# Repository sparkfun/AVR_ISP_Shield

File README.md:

SparkFun AVR ISP Shield
========================

[*SparkFun AVR ISP Shield (DEV-11168)*](https://www.sparkfun.com/products/11168)

This shield, once assembled, gives your Arduino a 28-pin ZIF (Zero Insertion Force) socket so it can grab onto unsuspecting ICs. 
The socket is wired to work directly with the ArduinoISP code, but burning bootloaders isn’t the only thing you can do with it. 
We’ve also connected the serial I/Os so that if you’re a programming ninja you can do cool tricks like programming ICs using the bootloader on-the-go.

Repository Contents
-------------------
* **/Hardware** - All Eagle design files (.brd, .sch)

License Information
-------------------
The hardware is released under [Creative Commons ShareAlike 4.0 International](https://creativecommons.org/licenses/by-sa/4.0/).

Distributed as-is; no warranty is given.

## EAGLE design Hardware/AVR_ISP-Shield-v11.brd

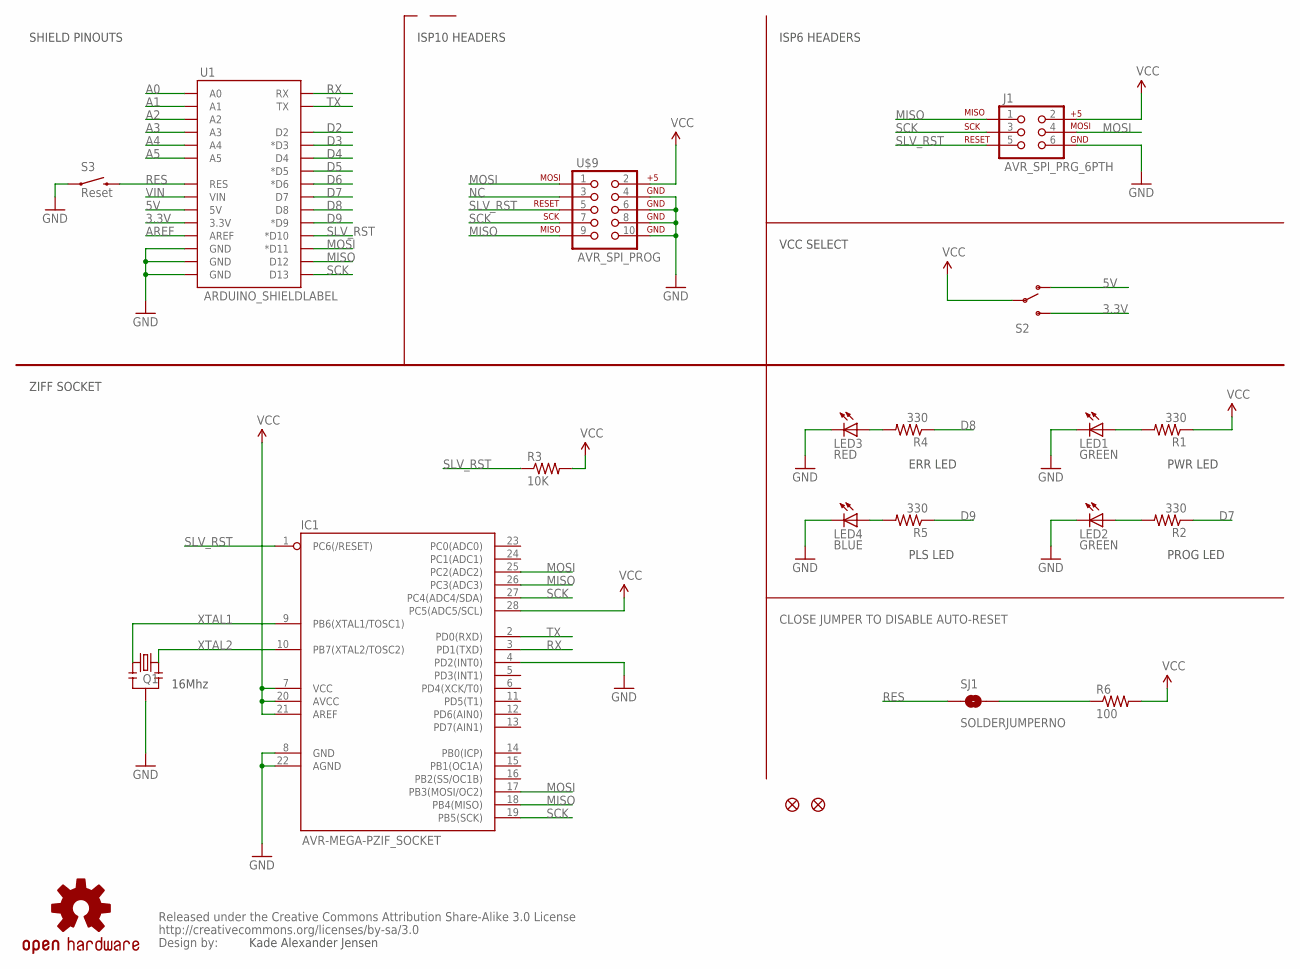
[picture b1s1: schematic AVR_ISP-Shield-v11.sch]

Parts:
$$U$1: CREATIVE_COMMONS
IC1: AVR-MEGA-PZIF_SOCKET; DIL28-3-ZIF_SOCKET
J1: AVR_SPI_PRG_6PTH; 2X3
JP5, JP6: FIDUCIAL1X2.5; FIDUCIAL-1X2.5
LED1, LED2: GREEN; LED-0603
LED3: RED; LED-0603
LED4: BLUE; LED-0603
Q1: 8/16/20MHz; RESONATOR-SMD
R1, R2, R4, R5: 330; 0402-RES
R3: 10K; 0402-RES
R6: 100; 0402-RES
S2: SWITCH-SPSTSMD; AYZ0202
S3: Reset; TACTILE_SWITCH_SMD
SJ1: SOLDERJUMPERNO; SJ_2S-NO
U1: ARDUINO_SHIELDLABEL; DUEMILANOVE_SHIELD
U$4: OSHW-LOGOS; OSHW-LOGO-S
U$9: AVR_SPI_PROG; AVR_ICSP

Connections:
3.3V: S2.3 (S), U1.3.3V
5V: S2.1 (O), U1.5V
A0: U1.A0
A1: U1.A1
A2: U1.A2
A3: U1.A3
A4: U1.A4
A5: U1.A5
AREF: U1.AREF
D2: U1.D2
D3: U1.D3 (*D3)
D4: U1.D4
D5: U1.D5 (*D5)
D6: U1.D6 (*D6)
D7: R2.1, U1.D7
D8: R4.1, U1.D8
D9: R5.1, U1.D9 (*D9)
GND: IC1.4 (PD2(INT0)), IC1.8 (GND), IC1.22 (AGND), J1.6, LED1.C, LED2.C, LED3.C, LED4.C, Q1.2, S3.1, U1.GND@0 (GND), U1.GND@1 (GND), U1.GND@2 (GND), U$9.4, U$9.6, U$9.8, U$9.10
MISO: IC1.18 (PB4(MISO)), IC1.26 (PC3(ADC3)), J1.1, U1.D12, U$9.9
MOSI: IC1.17 (PB3(MOSI/OC2)), IC1.25 (PC2(ADC2)), J1.4, U1.D11 (*D11), U$9.1
unnamed: LED1.A, R1.2
unnamed: LED2.A, R2.2
unnamed: LED3.A, R4.2
unnamed: LED4.A, R5.2
unnamed: R6.1, SJ1.2
NC: U$9.3
RES: S3.3 (2), SJ1.1, U1.RES
RX: IC1.3 (PD1(TXD)), U1.RX
SCK: IC1.19 (PB5(SCK)), IC1.27 (PC4(ADC4/SDA)), J1.3, U1.D13, U$9.7
SLV_RST: IC1.1 (PC6(/RESET)), J1.5, R3.1, U1.D10 (*D10), U$9.5
TX: IC1.2 (PD0(RXD)), U1.TX
VCC: IC1.7 (VCC), IC1.20 (AVCC), IC1.21 (AREF), IC1.28 (PC5(ADC5/SCL)), J1.2, R1.1, R3.2, R6.2, S2.2, U$9.2
VIN: U1.VIN
XTAL1: IC1.9 (PB6(XTAL1/TOSC1)), Q1.3
XTAL2: IC1.10 (PB7(XTAL2/TOSC2)), Q1.1

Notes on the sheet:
PWR LED
PROG LED
VCC SELECT
ISP6 HEADERS
ERR LED
PLS LED
16Mhz
Kade Alexander Jensen
ZIFF SOCKET
SHIELD PINOUTS
ISP10 HEADERS
CLOSE JUMPER TO DISABLE AUTO-RESET

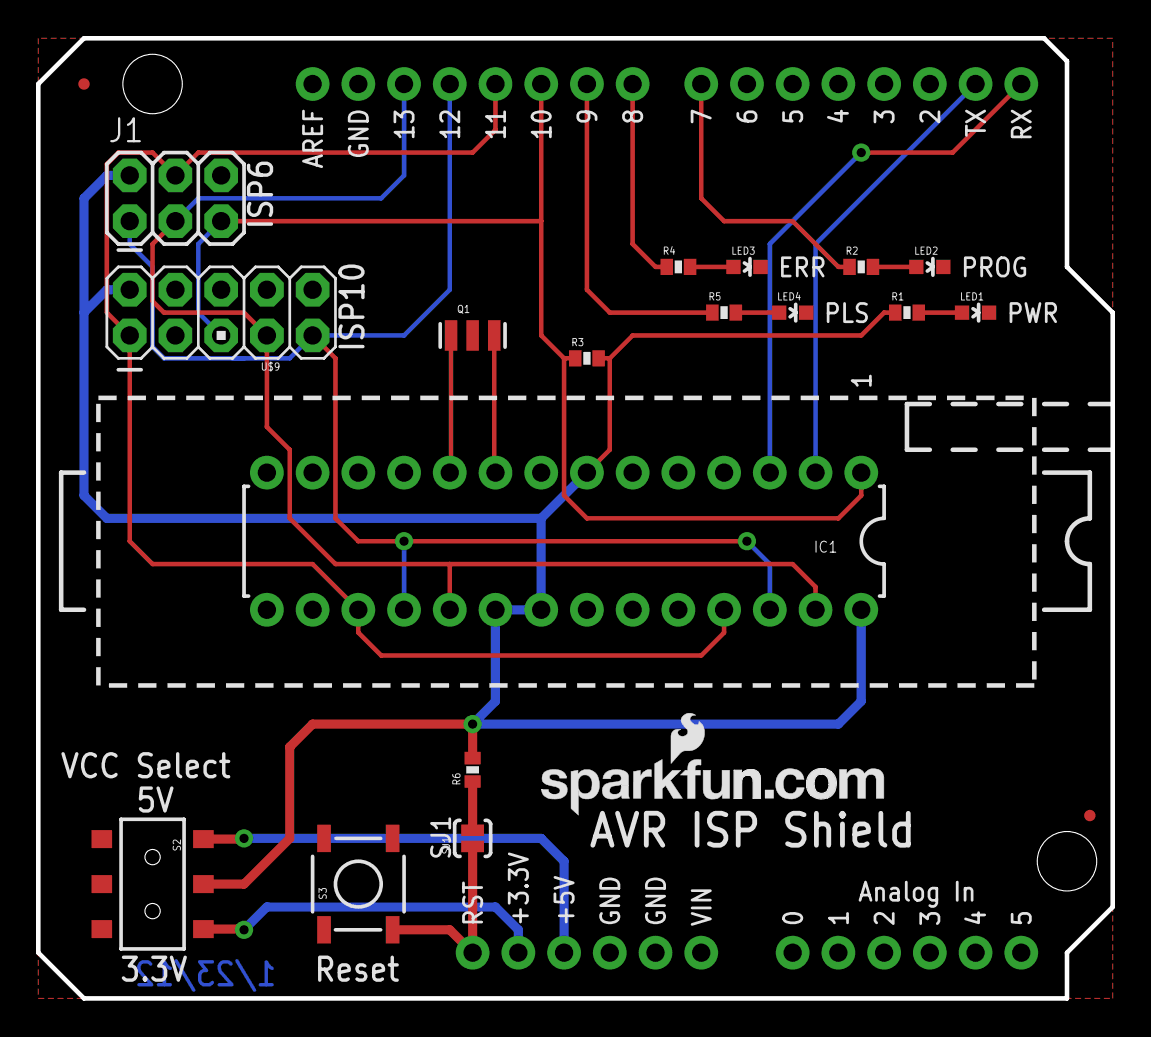
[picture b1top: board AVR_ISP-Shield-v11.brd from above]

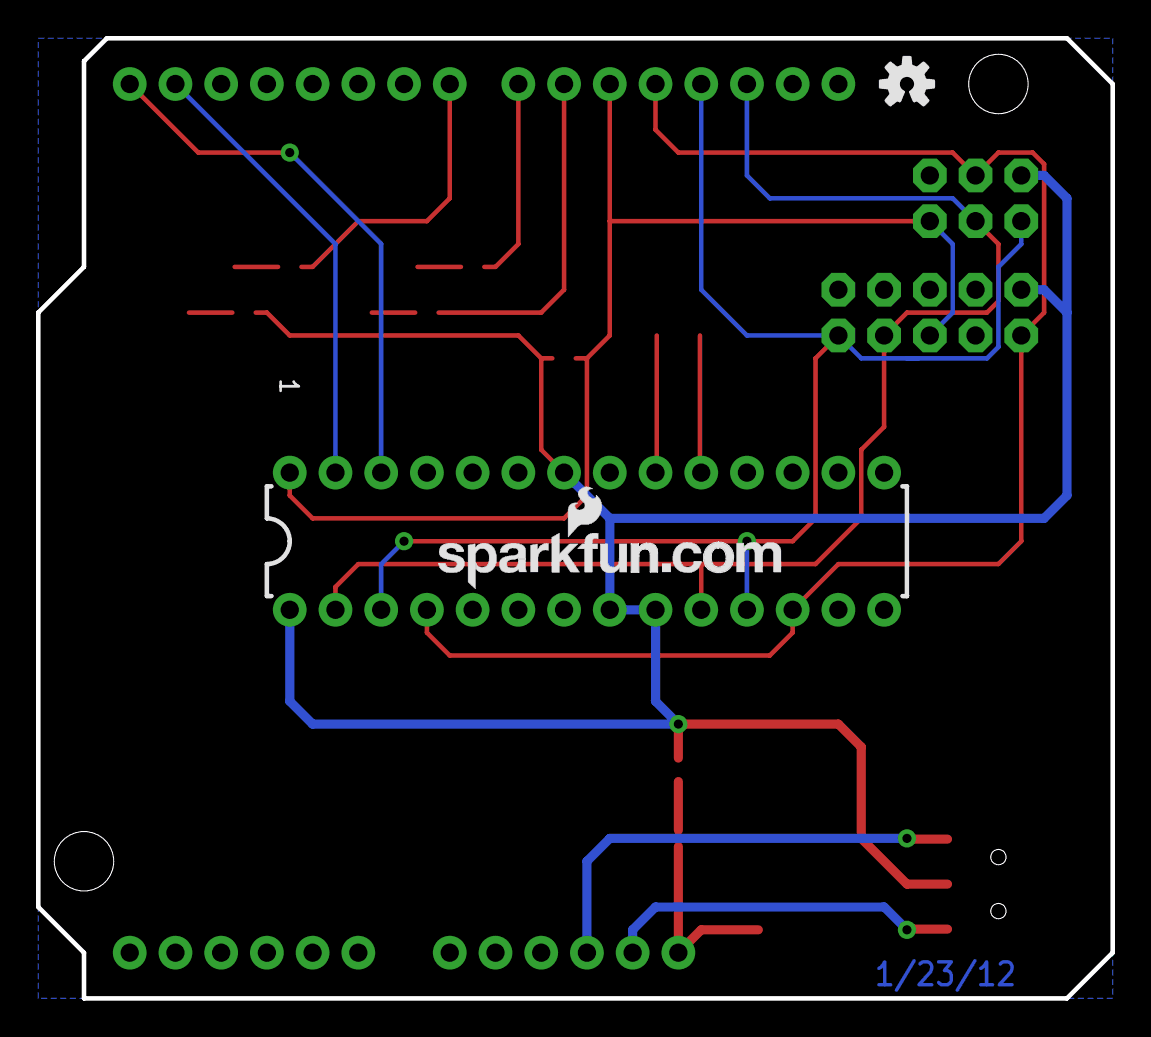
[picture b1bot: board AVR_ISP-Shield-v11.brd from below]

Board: 2 copper layers, 59.7 x 53.3 mm, 24 parts (2 on the bottom side), 21 nets.

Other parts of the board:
U$7, U$12: SFE-NEW-WEBLOGO

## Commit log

2015-03-09 Adding hardware files, readme links

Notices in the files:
parts and their libraries:
SparkFun: Released under the Creative Commons Attribution Share-Alike 3.0 License
SparkFun: http://creativecommons.org/licenses/by-sa/3.0
